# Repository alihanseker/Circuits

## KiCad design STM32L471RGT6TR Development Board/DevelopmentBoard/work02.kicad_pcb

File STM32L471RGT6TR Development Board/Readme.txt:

--------------------------------------------------
This Dev. Board developed by Alihan Şeker.

--------------------------------------------------
This circuit has a STM32L471RGT6TR microcontroller.This microcontroller 
is use Low power and you can use if you need low power and long battery life.
You can use a ST Link for programming and select boot mode with BOOT selection
division in the circuit. So flash memory or something can be use as system memory.

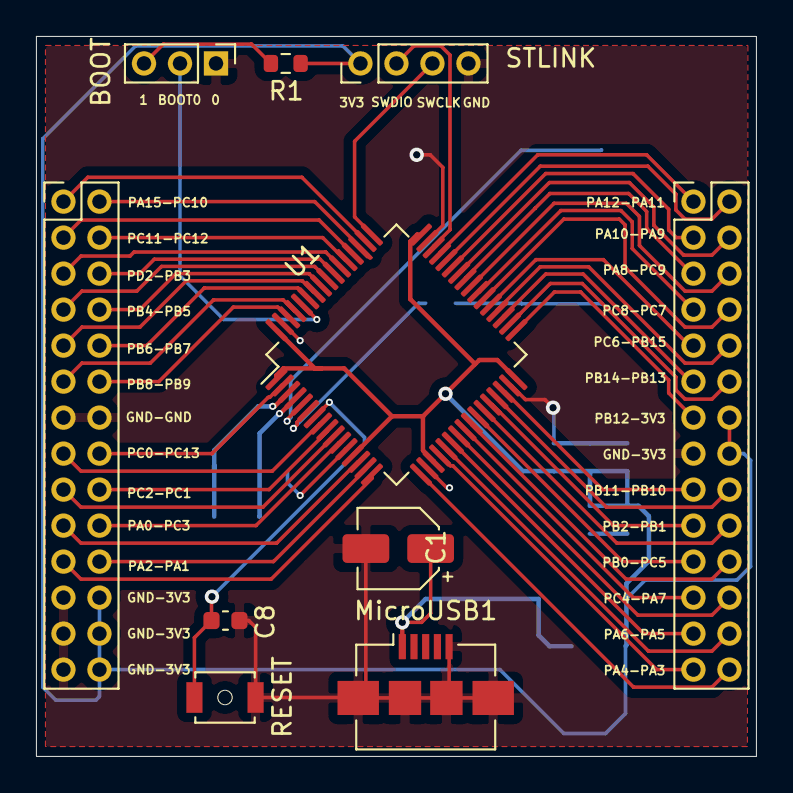
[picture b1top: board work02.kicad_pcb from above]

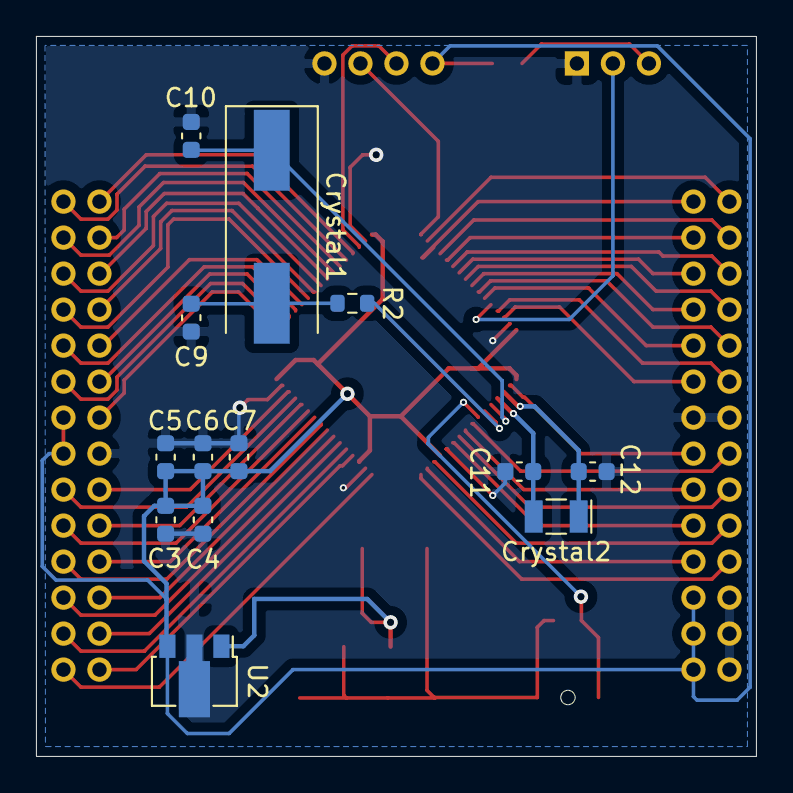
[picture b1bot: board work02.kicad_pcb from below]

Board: 2 copper layers, 40.0 x 40.0 mm, 23 parts (13 on the bottom side), 58 nets.

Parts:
BOOT: Conn_01x03; PinHeader_1x03_P2.00mm_Vertical
C1: 1uF; CP_Elec_4x3
C3, C4, C5, C7: 100nF; C_0603_1608Metric
C6: 10nF; C_0603_1608Metric
C8: 0.1uF; C_0603_1608Metric
C9, C10, C11, C12: 20pF; C_0603_1608Metric
CN1, CN2: Conn_02x14_Odd_Even; PinHeader_2x14_P2.00mm_Vertical
Crystal1: 8Mhz; Crystal_SMD_HC49-SD
Crystal2: 32.768kHz; Crystal_SMD_MicroCrystal_CC7V-T1A-2Pin_3.2x1.5mm
MicroUSB1: USB_B_Micro; USB_Micro-B_Amphenol_10104110_Horizontal
R1: 100k; R_0603_1608Metric
R2: 1k; R_0603_1608Metric
RESET: SW_Push; SW_SPST_B3U-1000P-B
STLINK: GND SWCLK SWDIO +3V3; PinHeader_1x04_P2.00mm_Vertical
U1: STM32L471RGT6TR; LQFP-64_10x10mm_P0.5mm
U2: MCP1754-3302E_SOT89; SOT-89-3

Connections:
+5V: C1.1, MicroUSB1.1, U2.1
BOOT0: BOOT.2, U1.60
GND: BOOT.1, C1.2, C3.1, C4.1, C5.1, C6.1, C7.1, C8.2, C9.2, C10.1, C11.2, C12.1, CN1.13, CN1.14, CN1.23, CN1.25, CN1.27, CN2.15, MicroUSB1.5, MicroUSB1.6, RESET.1, STLINK.4, U1.12, U1.18, U1.31, U1.47, U1.63, U2.2
unnamed: BOOT.3, R1.1
unnamed: C8.1, RESET.2, U1.7
unnamed: C9.1, Crystal1.2, R2.1
OSC32_IN: C12.2, Crystal2.1, U1.3
OSC32_OUT: C11.1, Crystal2.2, U1.4
OSC_IN: C10.2, Crystal1.1, U1.5
OSC_OUT: R2.2, U1.6
PA0: CN1.19, U1.14
PA1: CN1.22, U1.15
PA2: CN1.21, U1.16
PA3: CN2.28, U1.17
PA4: CN2.27, U1.20
PA5: CN2.26, U1.21
PA6: CN2.25, U1.22
PA7: CN2.24, U1.23
PA8: CN2.5, U1.41
PA9: CN2.4, U1.42
PA10: CN2.3, U1.43
PA11: CN2.2, U1.44
PA12: CN2.1, U1.45
PA15: CN1.1, U1.50
PB0: CN2.21, U1.26
PB1: CN2.20, U1.27
PB2: CN2.19, U1.28
PB3: CN1.6, U1.55
PB4: CN1.7, U1.56
PB5: CN1.8, U1.57
PB6: CN1.9, U1.58
PB7: CN1.10, U1.59
PB8: CN1.11, U1.61
PB9: CN1.12, U1.62
PB10: CN2.18, U1.29
PB11: CN2.17, U1.30
PB12: CN2.13, U1.33
PB13: CN2.12, U1.34
PB14: CN2.11, U1.35
PB15: CN2.10, U1.36
PC0: CN1.15, U1.8
PC1: CN1.18, U1.9
PC2: CN1.17, U1.10
PC3: CN1.20, U1.11
PC4: CN2.23, U1.24
PC5: CN2.22, U1.25
PC6: CN2.9, U1.37
PC7: CN2.8, U1.38
PC8: CN2.7, U1.39
PC9: CN2.6, U1.40
PC10: CN1.2, U1.51
PC11: CN1.3, U1.52
PC12: CN1.4, U1.53
PC13: CN1.16, U1.2
PD2: CN1.5, U1.54
SWCLK: STLINK.3, U1.49
SWDIO: STLINK.2, U1.46
VDD1: C3.2, C4.2, C5.2, C6.2, C7.2, CN1.24, CN1.26, CN1.28, CN2.14, CN2.16, R1.2, STLINK.1, U1.1, U1.13, U1.19, U1.32, U1.48, U1.64, U2.3

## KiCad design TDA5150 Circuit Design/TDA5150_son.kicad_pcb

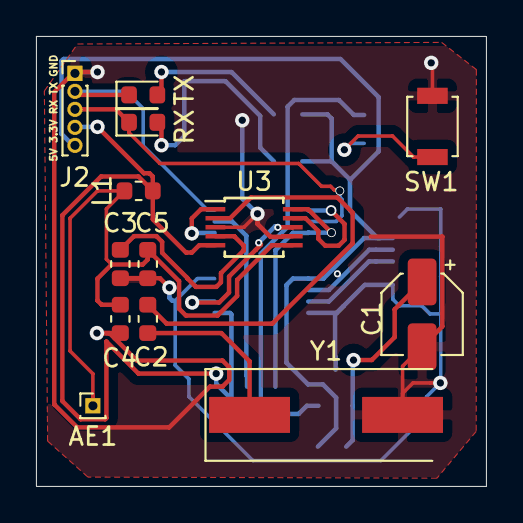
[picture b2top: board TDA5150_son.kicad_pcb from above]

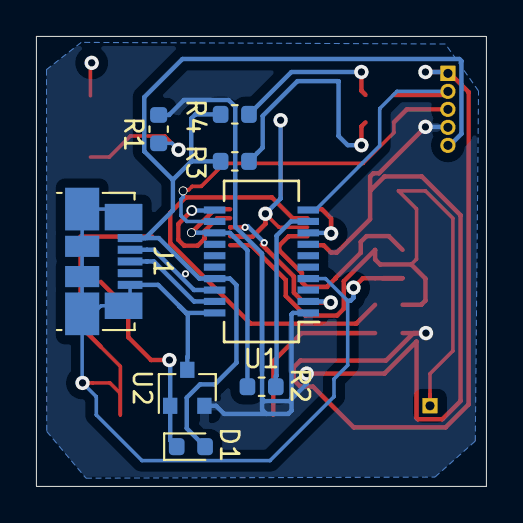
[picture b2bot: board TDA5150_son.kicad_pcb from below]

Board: 2 copper layers, 25.0 x 25.0 mm, 21 parts (8 on the bottom side), 20 nets.

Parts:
AE1: Antenna; PinHeader_1x01_P1.00mm_Vertical
C1: 0,1uF; CP_Elec_4x3
C2: 8.2pF; C_0603_1608Metric
C3: 100nF; C_0603_1608Metric
C4: 10pF; C_0603_1608Metric
C5: CP1; C_0603_1608Metric
D1: D_Schottky; D_0603_1608Metric
J1: USB_B_Micro; USB_Micro-B_Molex_47346-0001
J2: Conn_01x05_Male; PinHeader_1x05_P1.00mm_Vertical
L1: L; L_0603_1608Metric
R1, R2: 10k; R_0603_1608Metric
R3, R4: 1.5k; R_0603_1608Metric
RX: LED; LED_0603_1608Metric
SW1: SW_DIP_x01; SW_SPST_B3U-1000P
TX: LED; LED_0603_1608Metric
U1: PIC18F14K50-ISS; SSOP-20_3.9x8.7mm_P0.635mm
U2: NCV51460; SOT-23
U3: TDA5150; TSSOP-10_3x3mm_P0.5mm
Y1: Crystal; Crystal_SMD_HC49-SD

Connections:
+3V3: J2.4, L1.1, R1.1, U1.1, U2.2, U3.5
+5V: D1.2, J1.1, J2.5, R3.2, R4.2, U1.17
CLKOUT: U1.2, U3.8
D+: J1.3, U1.19
D-: J1.2, U1.18
DATA: R2.1, U1.13, U3.10
EN: U1.8, U3.1
GND: C1.2, C3.2, C4.2, C5.2, J1.5, J1.6, J2.1, SW1.1, U1.4, U1.20, U2.3, U3.3, U3.7, Y1.2
unnamed: AE1.1, C4.1, C5.1, L1.2, U3.6
unnamed: C1.1, D1.1, U2.1
unnamed: C2.1, U3.2
unnamed: C2.2, Y1.1
unnamed: C3.1, U3.4
unnamed: R3.1, RX.2
unnamed: R4.1, TX.2
unnamed: R1.2, SW1.2
unnamed: R2.2, U1.9
RX: J2.3, RX.1, U1.12
SCK: U1.11, U3.9
TX: J2.2, TX.1, U1.10

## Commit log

2020-02-17 KiCAD
    Designed in KiCAD
2020-02-17 Set theme jekyll-theme-time-machine
2020-11-30 STM32L471RGT6TR Development Circuit
